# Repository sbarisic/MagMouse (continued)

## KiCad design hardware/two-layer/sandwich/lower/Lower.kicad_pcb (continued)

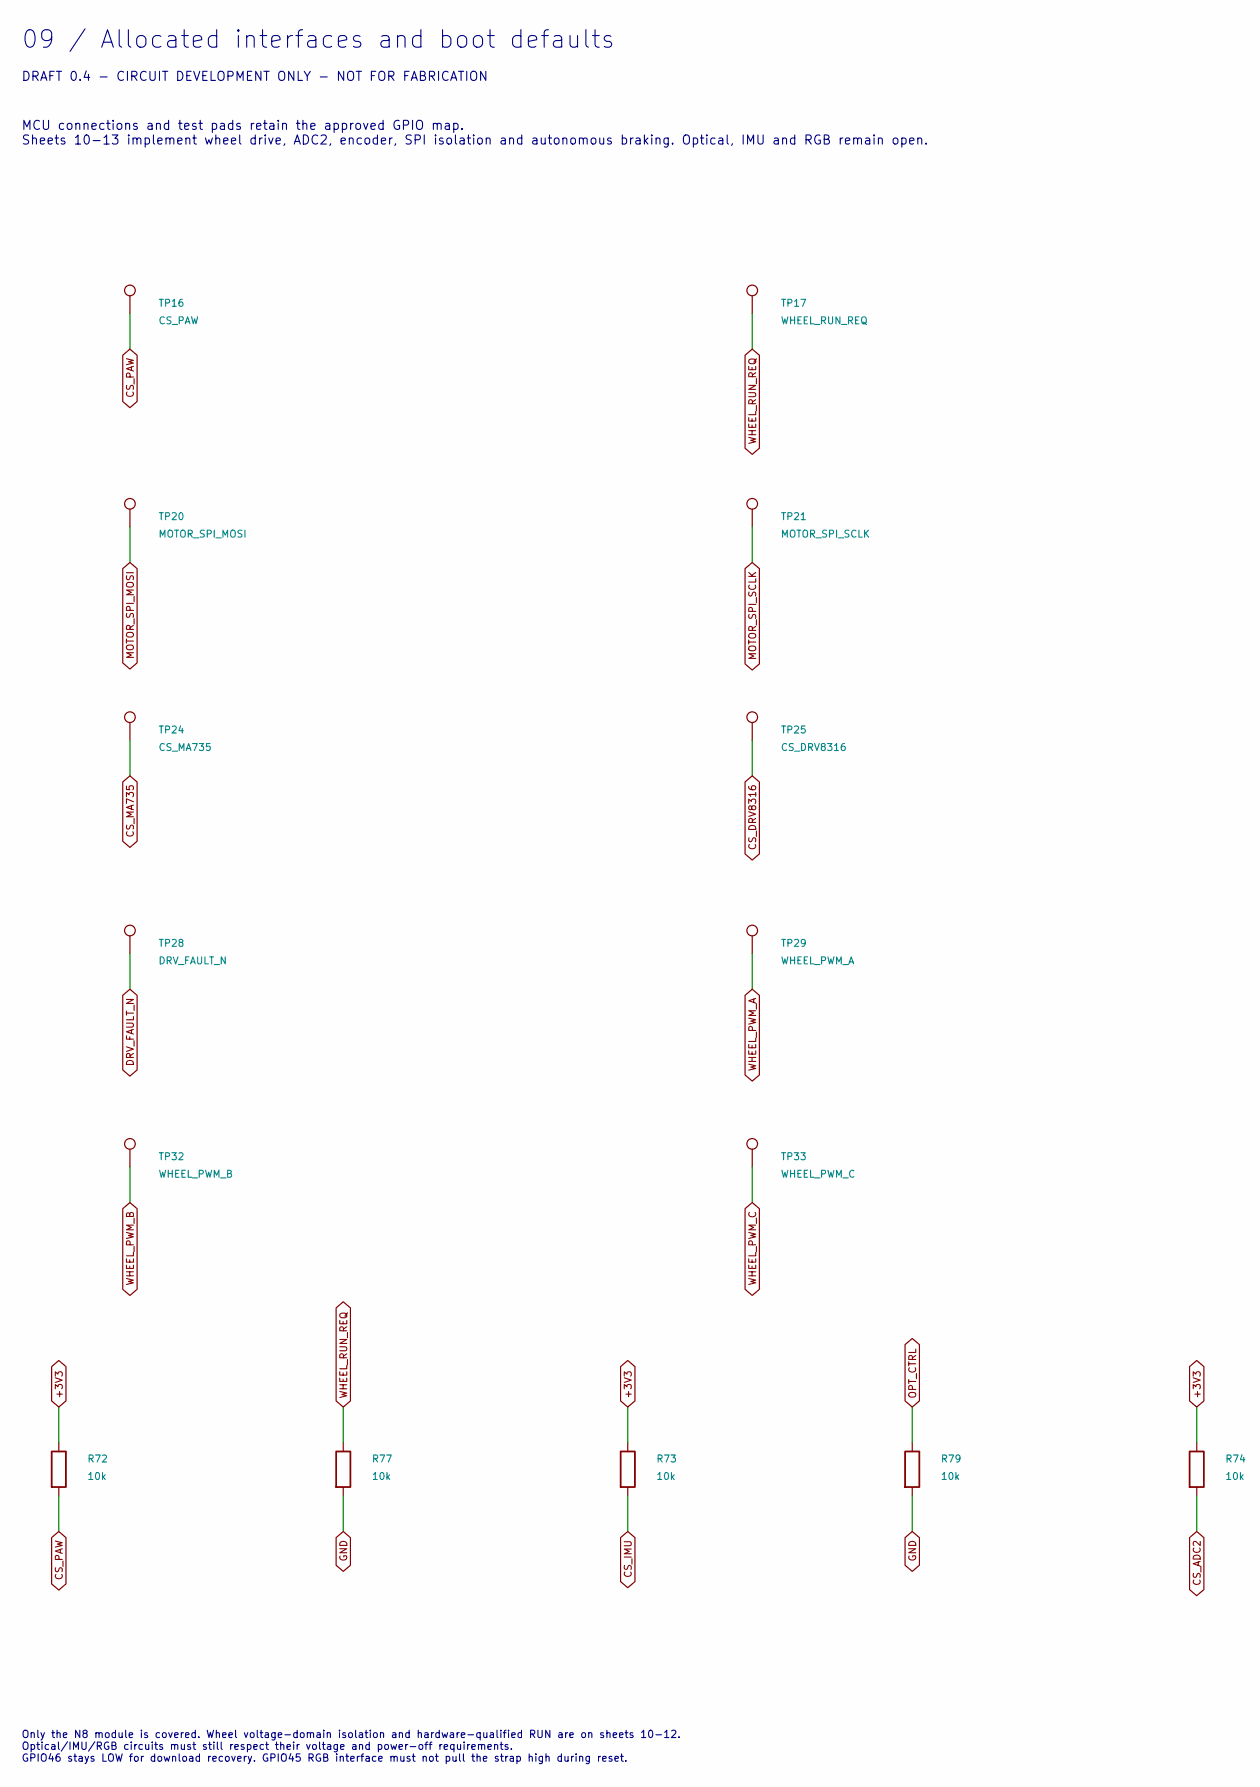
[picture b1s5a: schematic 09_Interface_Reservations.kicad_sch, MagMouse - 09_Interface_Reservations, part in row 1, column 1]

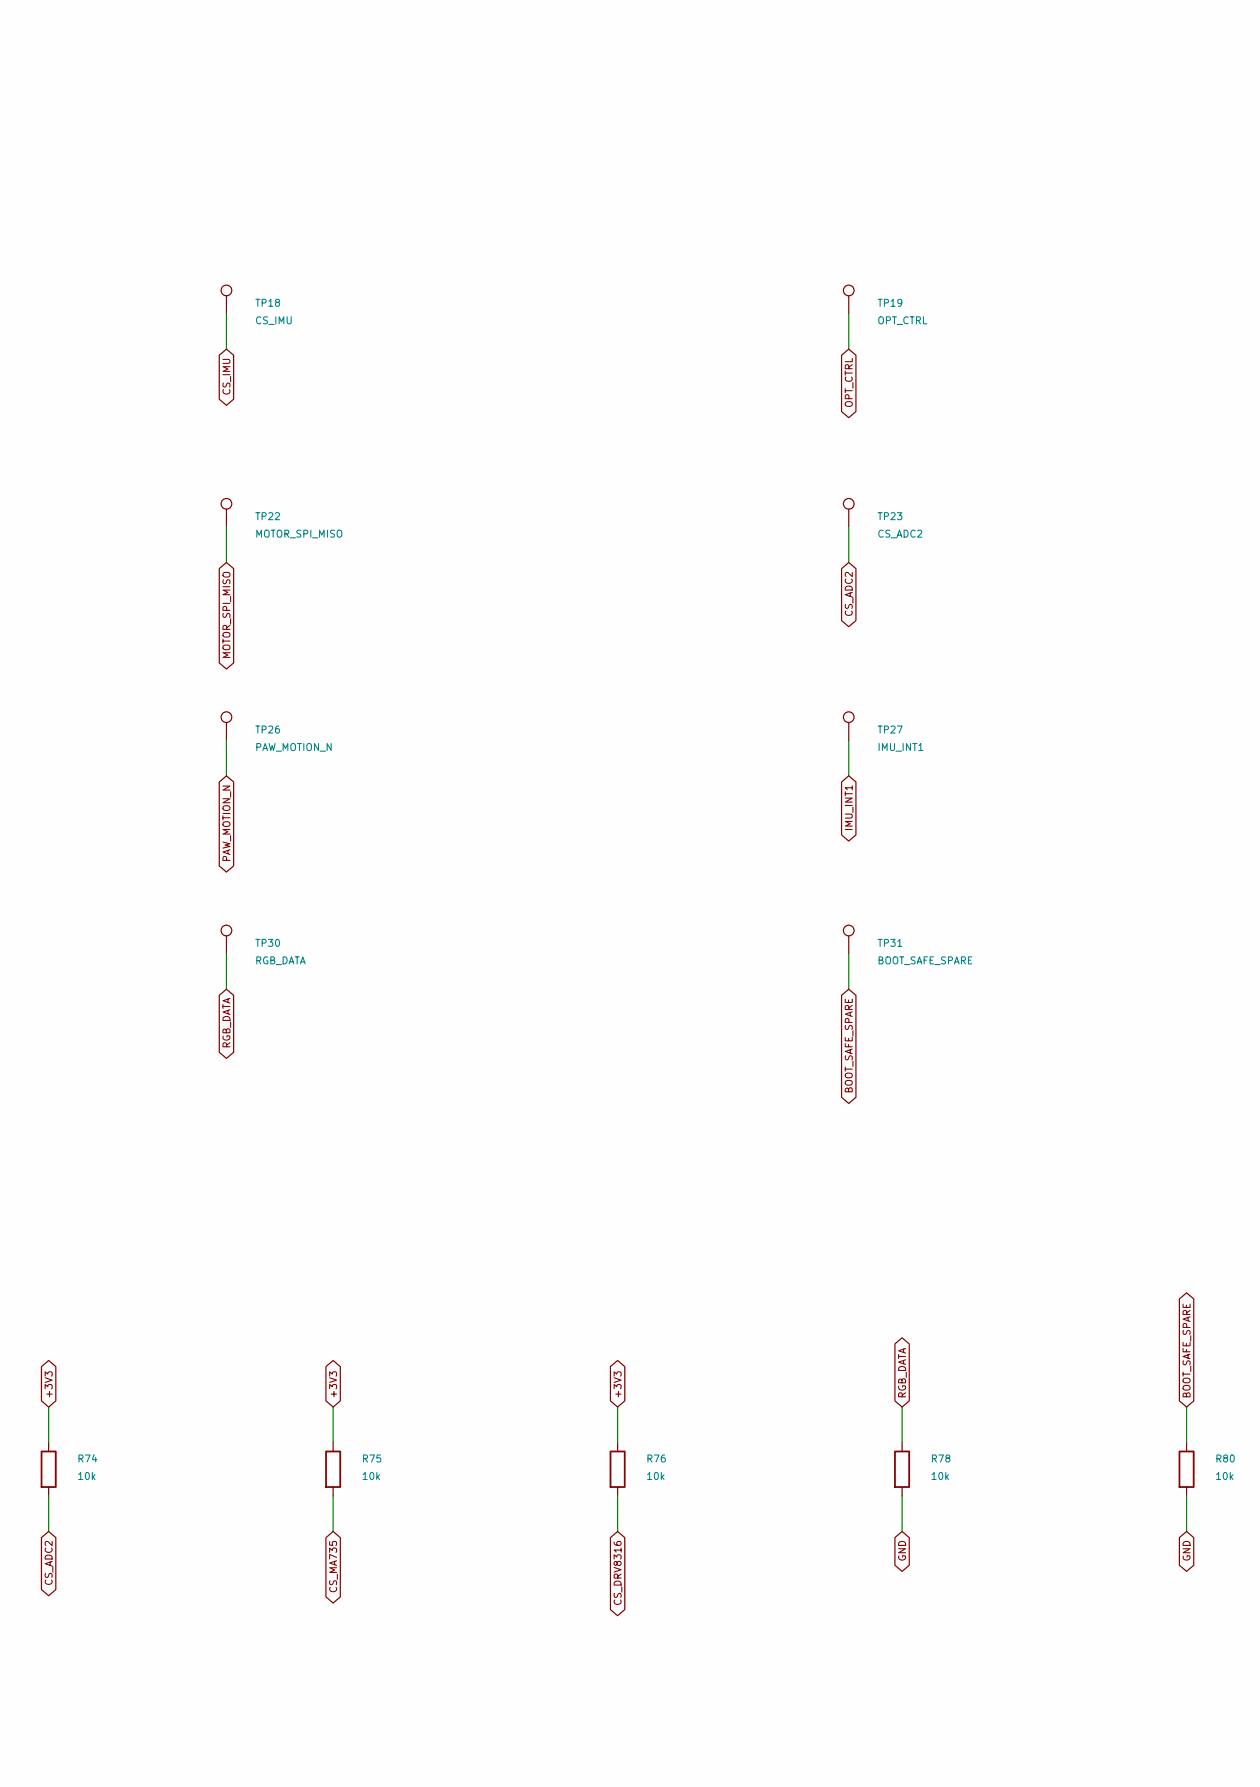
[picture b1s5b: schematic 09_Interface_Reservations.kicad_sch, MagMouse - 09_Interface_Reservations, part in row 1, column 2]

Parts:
R72, R73, R74, R75, R76, R77, R78, R79, R80: 10k; R_1206_3216Metric; Rating 0.25 W, 1%; MPN RC1206FR-0710KL
TP16: CS_PAW; TestPoint_Pad_D1.0mm
TP17: WHEEL_RUN_REQ; TestPoint_Pad_D1.0mm
TP18: CS_IMU; TestPoint_Pad_D1.0mm
TP19: OPT_CTRL; TestPoint_Pad_D1.0mm
TP20: MOTOR_SPI_MOSI; TestPoint_Pad_D1.0mm
TP21: MOTOR_SPI_SCLK; TestPoint_Pad_D1.0mm
TP22: MOTOR_SPI_MISO; TestPoint_Pad_D1.0mm
TP23: CS_ADC2; TestPoint_Pad_D1.0mm
TP24: CS_MA735; TestPoint_Pad_D1.0mm
TP25: CS_DRV8316; TestPoint_Pad_D1.0mm
TP26: PAW_MOTION_N; TestPoint_Pad_D1.0mm
TP27: IMU_INT1; TestPoint_Pad_D1.0mm
TP28: DRV_FAULT_N; TestPoint_Pad_D1.0mm
TP29: WHEEL_PWM_A; TestPoint_Pad_D1.0mm
TP30: RGB_DATA; TestPoint_Pad_D1.0mm
TP31: BOOT_SAFE_SPARE; TestPoint_Pad_D1.0mm
TP32: WHEEL_PWM_B; TestPoint_Pad_D1.0mm
TP33: WHEEL_PWM_C; TestPoint_Pad_D1.0mm

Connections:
+3V3: R72.1, R73.1, R74.1, R75.1, R76.1; also elsewhere on the board
BOOT_SAFE_SPARE: R80.1, TP31.1; also elsewhere on the board
CS_ADC2: R74.2, TP23.1; also elsewhere on the board
CS_DRV8316: R76.2, TP25.1; also elsewhere on the board
CS_IMU: R73.2, TP18.1; also elsewhere on the board
CS_MA735: R75.2, TP24.1; also elsewhere on the board
CS_PAW: R72.2, TP16.1; also elsewhere on the board
DRV_FAULT_N: TP28.1; also elsewhere on the board
GND: R77.2, R78.2, R79.2, R80.2; also elsewhere on the board
IMU_INT1: TP27.1; also elsewhere on the board
MOTOR_SPI_MISO: TP22.1; also elsewhere on the board
MOTOR_SPI_MOSI: TP20.1; also elsewhere on the board
MOTOR_SPI_SCLK: TP21.1; also elsewhere on the board
OPT_CTRL: R79.1, TP19.1; also elsewhere on the board
PAW_MOTION_N: TP26.1; also elsewhere on the board
RGB_DATA: R78.1, TP30.1; also elsewhere on the board
WHEEL_PWM_A: TP29.1; also elsewhere on the board
WHEEL_PWM_B: TP32.1; also elsewhere on the board
WHEEL_PWM_C: TP33.1; also elsewhere on the board
WHEEL_RUN_REQ: R77.1, TP17.1; also elsewhere on the board

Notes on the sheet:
09 / Allocated interfaces and boot defaults
DRAFT 0.4 - CIRCUIT DEVELOPMENT ONLY - NOT FOR FABRICATION
MCU connections and test pads retain the approved GPIO map. Sheets 10-13 implement wheel drive, ADC2, encoder, SPI isolation and autonomous braking. Optical, IMU and RGB remain open.
Only the N8 module is covered. Wheel voltage-domain isolation and hardware-qualified RUN are on sheets 10-12. Optical/IMU/RGB circuits must still respect their voltage and power-off requirements. GPIO46 stays LOW for download recovery. GPIO45 RGB interface must not pull the strap high during reset.

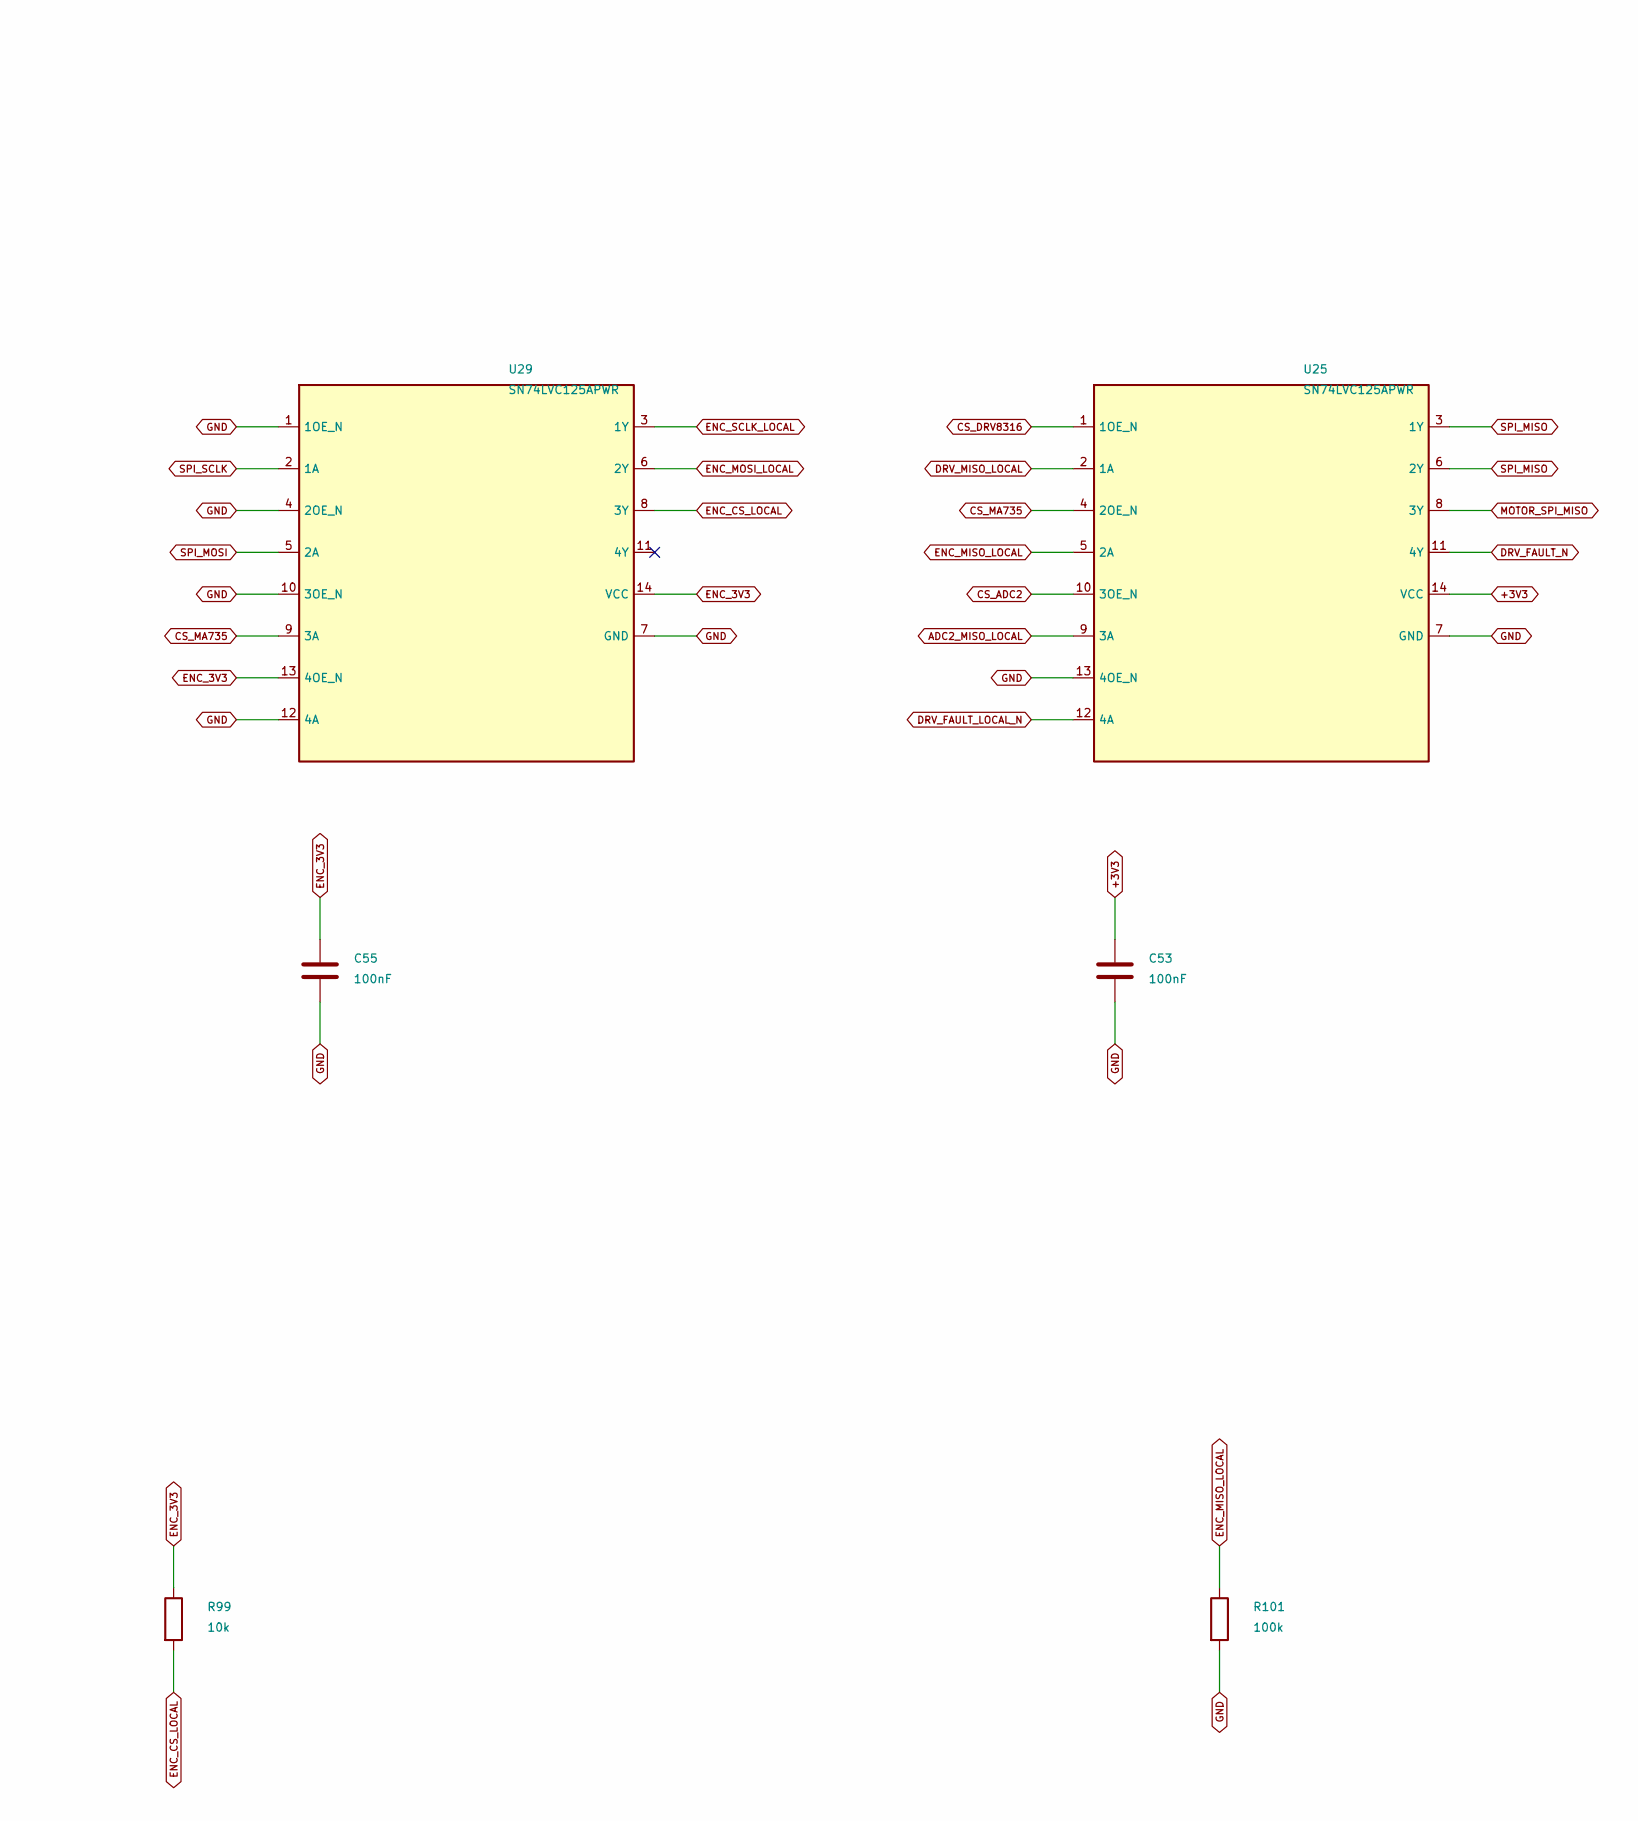
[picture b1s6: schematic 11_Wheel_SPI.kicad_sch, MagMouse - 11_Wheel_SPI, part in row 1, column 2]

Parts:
C53, C55: 100nF; C_1206_3216Metric; Rating 50 V, X7R, 10%; MPN CC1206KRX7R9BB104
R99: 10k; R_1206_3216Metric; Rating 0.25 W, 1%; MPN RC1206FR-0710KL
R101: 100k; R_1206_3216Metric; Rating 0.25 W, 1%; MPN RC1206FR-07100KL
U25, U29: SN74LVC125APWR; TSSOP-14_4.4x5mm_P0.65mm; MPN SN74LVC125APWR; LCSC C7813

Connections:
+3V3: C53.1, U25.14 (VCC); also elsewhere on the board
ADC2_MISO_LOCAL: U25.9 (3A); also elsewhere on the board
CS_ADC2: U25.10 (3OE_N); also elsewhere on the board
CS_DRV8316: U25.1 (1OE_N); also elsewhere on the board
CS_MA735: U25.4 (2OE_N), U29.9 (3A); also elsewhere on the board
DRV_FAULT_LOCAL_N: U25.12 (4A); also elsewhere on the board
DRV_FAULT_N: U25.11 (4Y); also elsewhere on the board
DRV_MISO_LOCAL: U25.2 (1A); also elsewhere on the board
ENC_3V3: C55.1, R99.1, U29.13 (4OE_N), U29.14 (VCC); also elsewhere on the board
ENC_CS_LOCAL: R99.2, U29.8 (3Y); also elsewhere on the board
ENC_MISO_LOCAL: R101.1, U25.5 (2A); also elsewhere on the board
ENC_MOSI_LOCAL: U29.6 (2Y); also elsewhere on the board
ENC_SCLK_LOCAL: U29.3 (1Y); also elsewhere on the board
GND: C53.2, C55.2, R101.2, U25.7 (GND), U25.13 (4OE_N), U29.1 (1OE_N), U29.4 (2OE_N), U29.7 (GND), U29.10 (3OE_N), U29.12 (4A); also elsewhere on the board
MOTOR_SPI_MISO: U25.8 (3Y); also elsewhere on the board
SPI_MISO: U25.3 (1Y), U25.6 (2Y); also elsewhere on the board
SPI_MOSI: U29.5 (2A); also elsewhere on the board
SPI_SCLK: U29.2 (1A); also elsewhere on the board

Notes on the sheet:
11_Wheel_SPI - Main owned components only See 18_Wheel_Harness for connector/bias additions; see INTERFACE_REVIEW.md for limits.

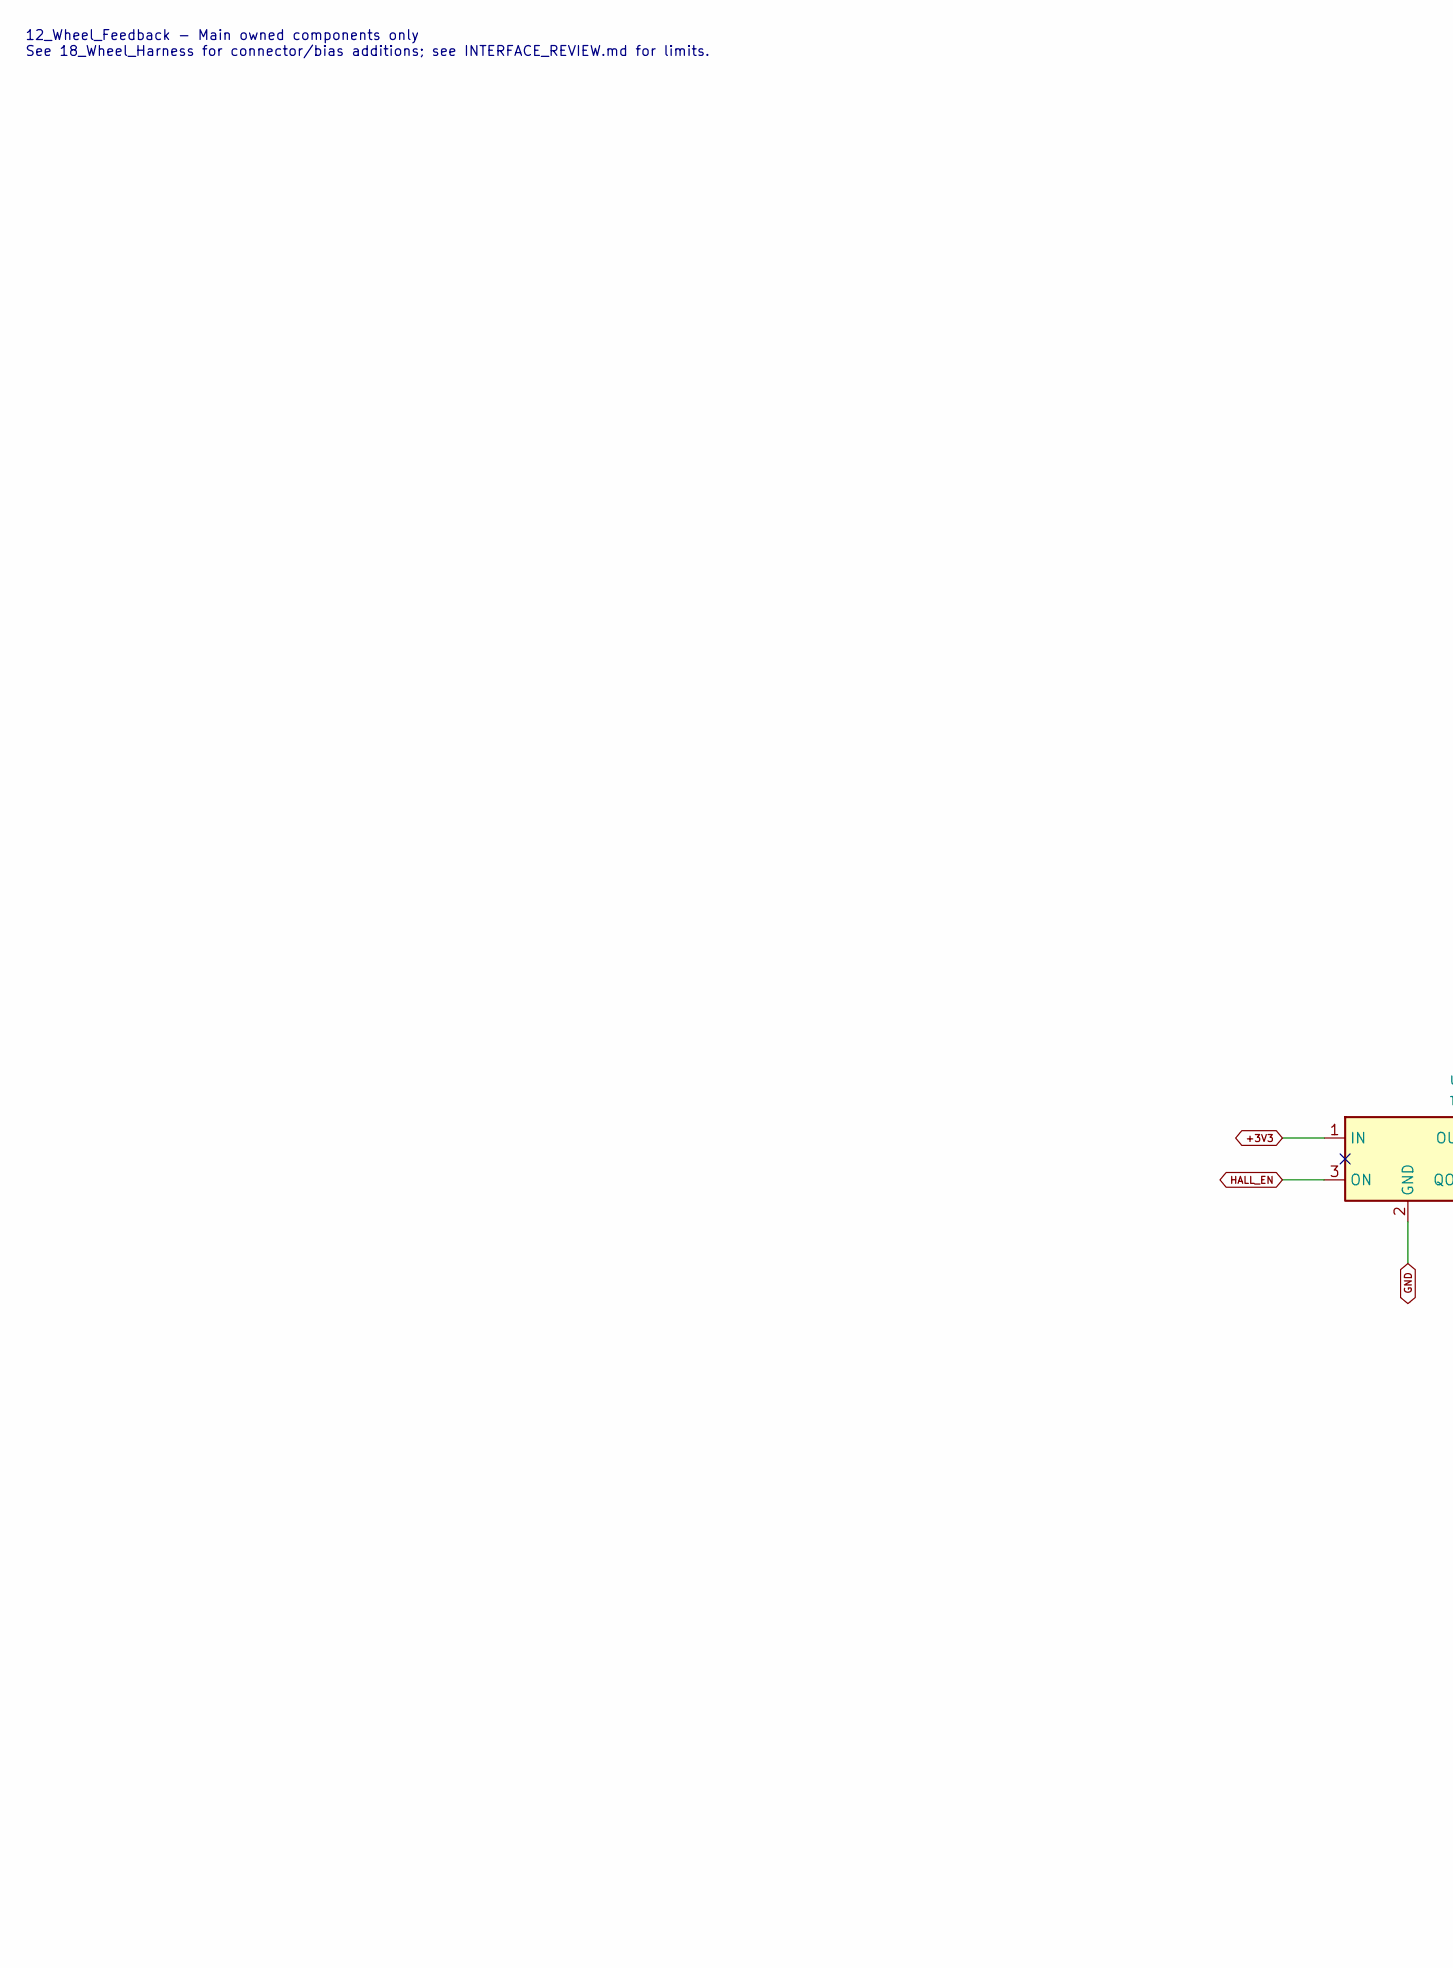
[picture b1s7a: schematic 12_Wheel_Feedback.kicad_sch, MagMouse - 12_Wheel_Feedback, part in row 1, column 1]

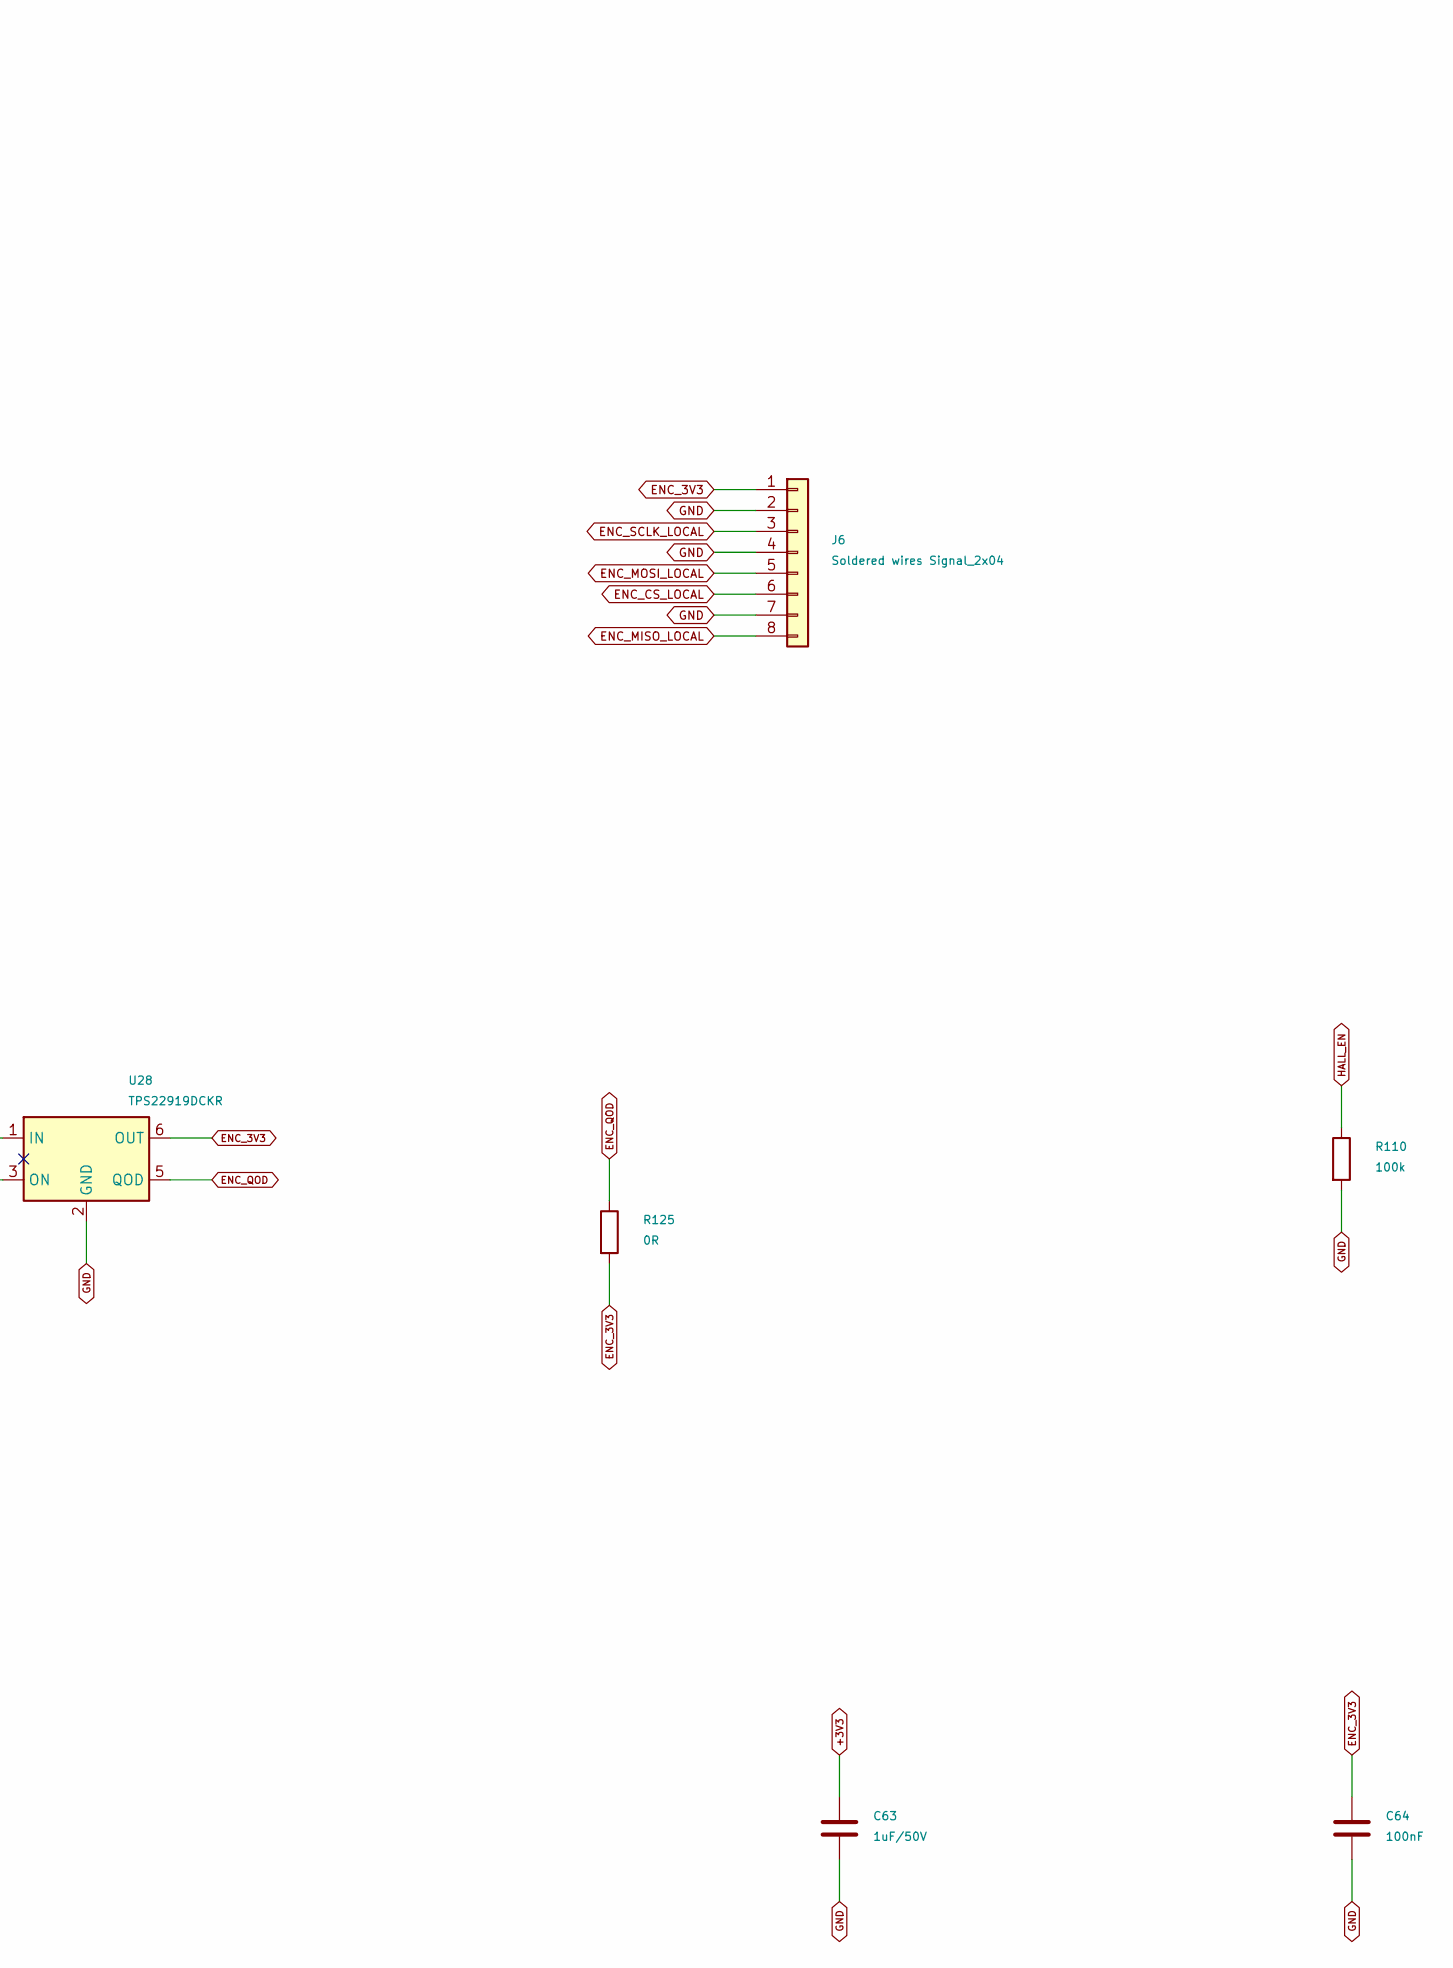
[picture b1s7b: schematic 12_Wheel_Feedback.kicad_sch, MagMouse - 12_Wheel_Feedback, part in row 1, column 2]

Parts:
C63: 1uF/50V; C_1206_3216Metric; Rating 50 V, X7R, 10%; MPN CL31B105KBHNNNE
C64: 100nF; C_1206_3216Metric; Rating 50 V, X7R, 10%; MPN CC1206KRX7R9BB104
J6: Soldered wires Signal_2x04; Wire_Signal_2x04_P2.54mm
R110: 100k; R_1206_3216Metric; Rating 0.25 W, 1%; MPN RC1206FR-07100KL
R125: 0R; R_1206_3216Metric; Rating Jumper, 2 A; MPN RC1206JR-070RL
U28: TPS22919DCKR; SOT-363_SC-70-6; MPN TPS22919DCKR; LCSC C2149796

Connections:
+3V3: C63.1, U28.1 (IN); also elsewhere on the board
ENC_3V3: C64.1, J6.1, R125.2, U28.6 (OUT); also elsewhere on the board
ENC_CS_LOCAL: J6.6; also elsewhere on the board
ENC_MISO_LOCAL: J6.8; also elsewhere on the board
ENC_MOSI_LOCAL: J6.5; also elsewhere on the board
ENC_QOD: R125.1, U28.5 (QOD)
ENC_SCLK_LOCAL: J6.3; also elsewhere on the board
GND: C63.2, C64.2, J6.2, J6.4, J6.7, R110.2, U28.2 (GND); also elsewhere on the board
HALL_EN: R110.1, U28.3 (ON); also elsewhere on the board

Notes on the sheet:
12_Wheel_Feedback - Main owned components only See 18_Wheel_Harness for connector/bias additions; see INTERFACE_REVIEW.md for limits.

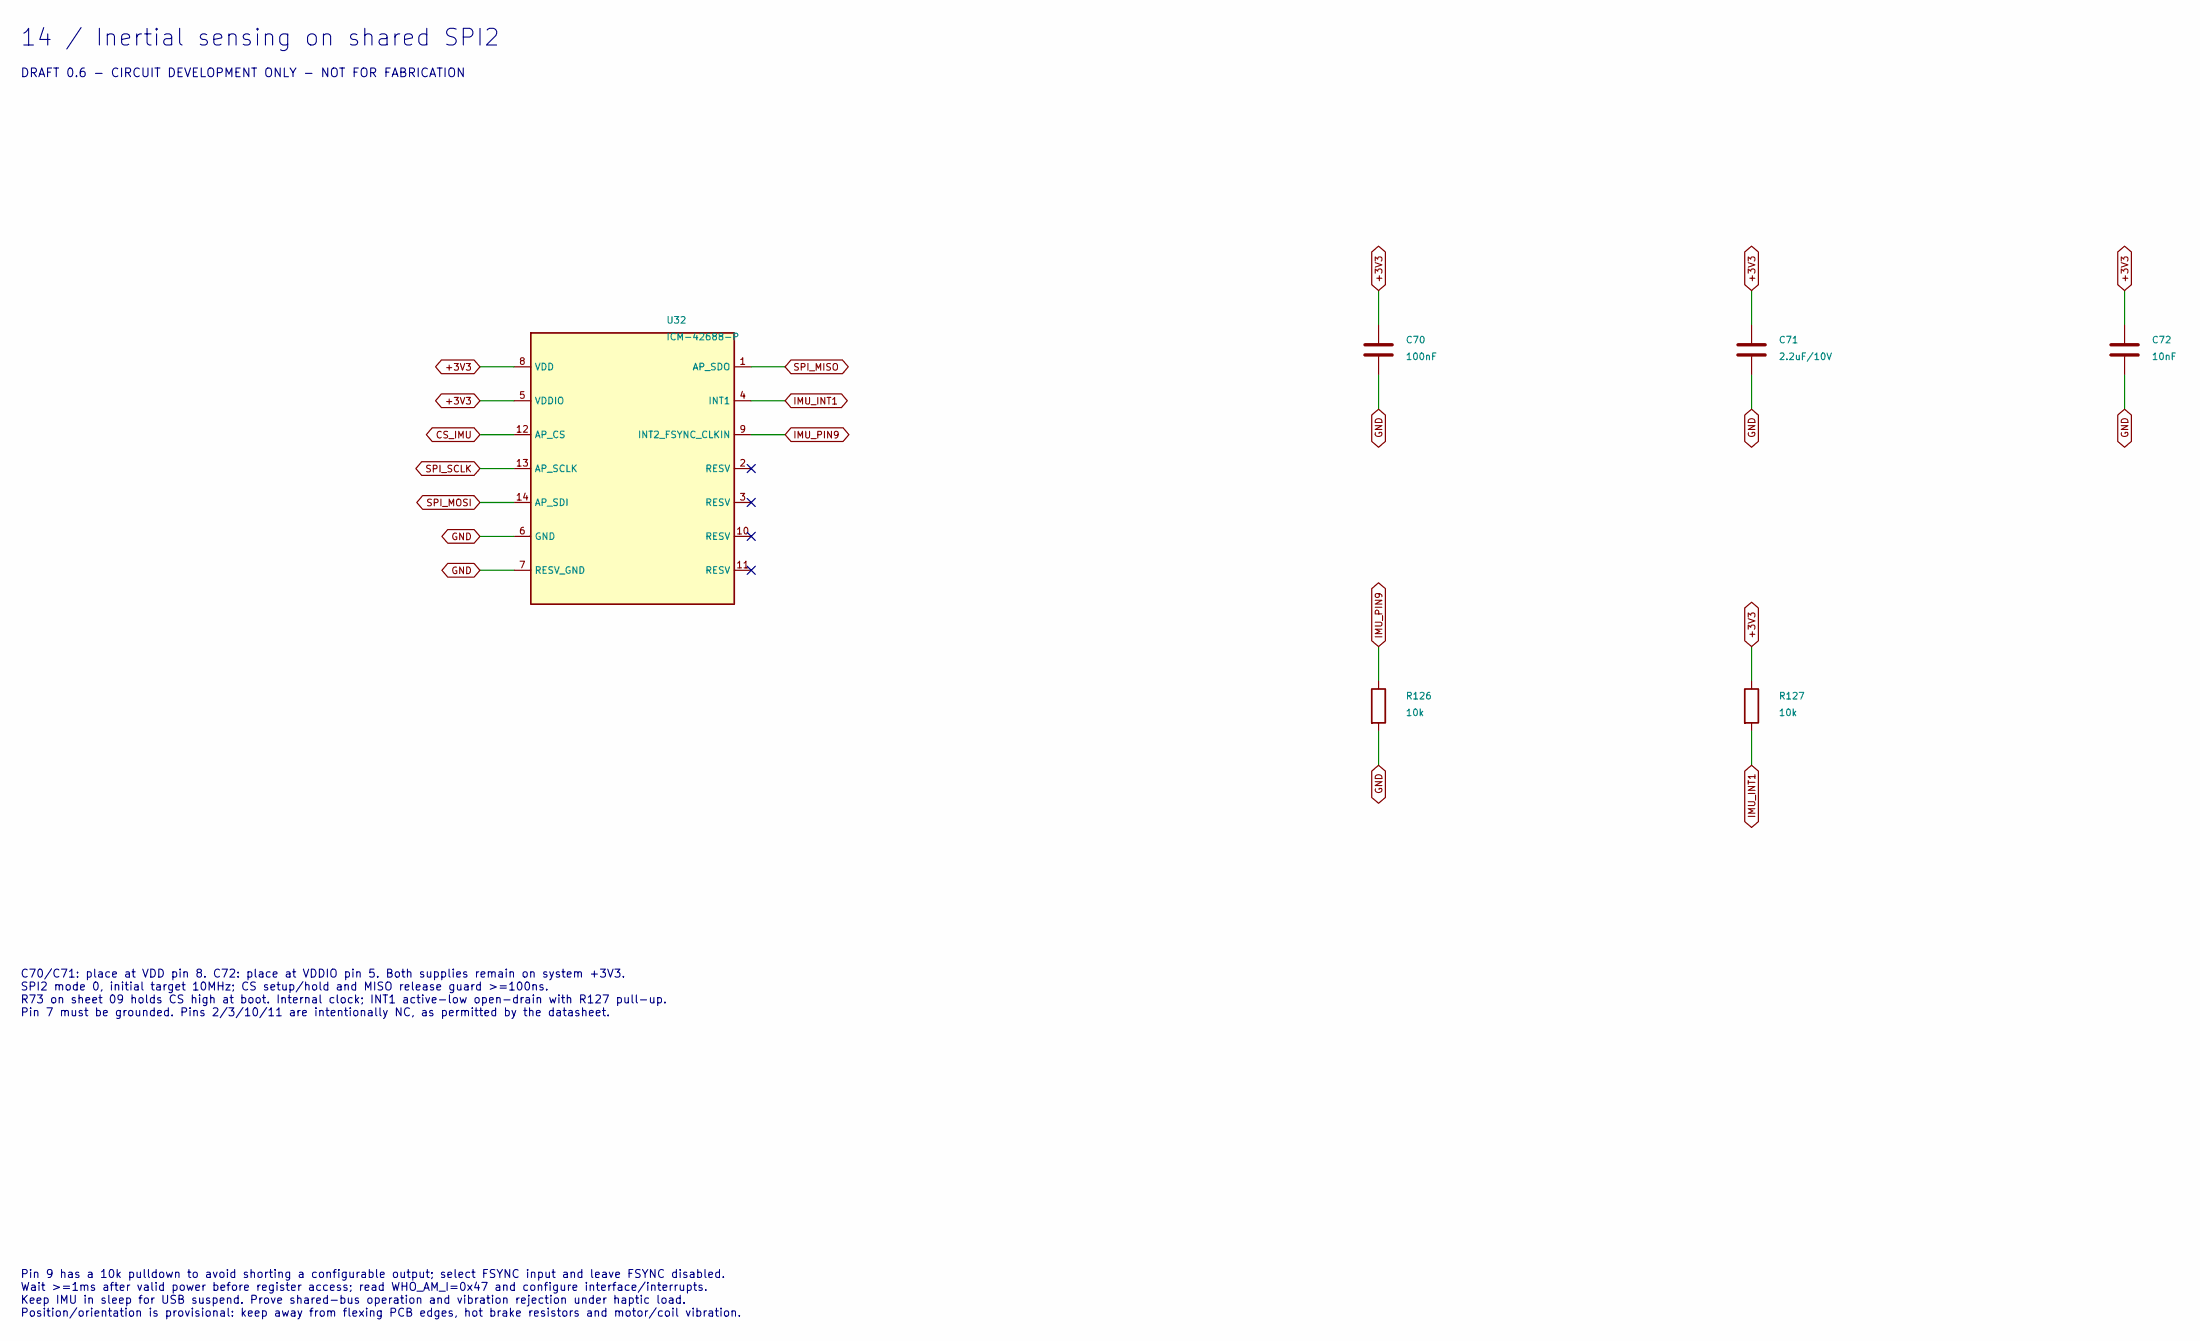
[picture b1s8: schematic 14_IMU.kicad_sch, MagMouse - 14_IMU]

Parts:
C70: 100nF; C_1206_3216Metric; Rating 50 V, X7R, 10%; MPN CC1206KRX7R9BB104
C71: 2.2uF/10V; C_1206_3216Metric; Rating 25 V, X7R, 10%; MPN CL31B225KAHNNNE
C72: 10nF; C_1206_3216Metric_OneSideSilk; Rating 50 V, X7R, 10%; MPN CC1206KRX7R9BB103
R126, R127: 10k; R_1206_3216Metric; Rating 0.25 W, 1%; MPN RC1206FR-0710KL
U32: ICM-42688-P; LGA-14_3x2.5mm_P0.5mm_LayoutBorder3x4y; MPN ICM-42688-P; LCSC C1850418

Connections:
+3V3: C70.1, C71.1, C72.1, R127.1, U32.5 (VDDIO), U32.8 (VDD); also elsewhere on the board
CS_IMU: U32.12 (AP_CS); also elsewhere on the board
GND: C70.2, C71.2, C72.2, R126.2, U32.6 (GND), U32.7 (RESV_GND); also elsewhere on the board
IMU_INT1: R127.2, U32.4 (INT1); also elsewhere on the board
IMU_PIN9: R126.1, U32.9 (INT2_FSYNC_CLKIN)
SPI_MISO: U32.1 (AP_SDO); also elsewhere on the board
SPI_MOSI: U32.14 (AP_SDI); also elsewhere on the board
SPI_SCLK: U32.13 (AP_SCLK); also elsewhere on the board

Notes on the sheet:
14 / Inertial sensing on shared SPI2
DRAFT 0.6 - CIRCUIT DEVELOPMENT ONLY - NOT FOR FABRICATION
C70/C71: place at VDD pin 8. C72: place at VDDIO pin 5. Both supplies remain on system +3V3. SPI2 mode 0, initial target 10MHz; CS setup/hold and MISO release guard >=100ns. R73 on sheet 09 holds CS high at boot. Internal clock; INT1 active-low open-drain with R127 pull-up. Pin 7 must be grounded. 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
Pin 9 has a 10k pulldown to avoid shorting a configurable output; select FSYNC input and leave FSYNC disabled. Wait >=1ms after valid power before register access; read WHO_AM_I=0x47 and configure interface/interrupts. Keep IMU in sleep for USB suspend. Prove shared-bus operation and vibration reje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

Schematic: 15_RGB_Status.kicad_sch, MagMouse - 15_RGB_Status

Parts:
C73, C74: 10uF/25V; C_1206_3216Metric; Rating 25 V, X5R, 10%; MPN CL31A106KAHNNNE
C75, C76: 100nF; C_1206_3216Metric; Rating 50 V, X7R, 10%; MPN CC1206KRX7R9BB104
D5: SK6805-EC15; OPSCO_SK6805_EC15; MPN SK6805-EC15; LCSC C2890035
R128: 330R; R_1206_3216Metric; Rating 0.25 W, 1%; MPN RC1206FR-07330RL
R129: 100k; R_1206_3216Metric; Rating 0.25 W, 1%; MPN RC1206FR-07100KL
R130: 10k; R_1206_3216Metric; Rating 0.25 W, 1%; MPN RC1206FR-0710KL
TP38: RGB_5V; TestPoint_Pad_D1.0mm
TP39: RGB_DIN; TestPoint_Pad_D1.0mm
U33: TPS7A2450DBVR; SOT-23-5; MPN TPS7A2450DBVR; LCSC C2864436
U34: SN74LV1T34DBVR; SOT-23-5; MPN SN74LV1T34DBVR; LCSC C100024

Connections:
GND: C73.2, C74.2, C75.2, C76.2, D5.4 (GND), R129.2, R130.2, U33.2 (GND), U34.3 (GND); also elsewhere on the board
HALL_EN: U33.3 (EN); also elsewhere on the board
PWR_5V: C73.1, U33.1 (IN); also elsewhere on the board
RGB_5V: C74.1, C75.1, C76.1, D5.2 (VDD), R130.1, TP38.1, U33.5 (OUT), U34.5 (VCC)
RGB_BUFFER_OUT: R128.1, U34.4 (Y)
RGB_DATA: U34.2 (A); also elsewhere on the board
RGB_DIN: D5.1 (DIN), R128.2, R129.1, TP39.1

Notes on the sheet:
15 / Single-data-pin status LED with switched protected supply
DRAFT 0.6 - CIRCUIT DEVELOPMENT ONLY - NOT FOR FABRICATION
U33 caps the LED rail near 5V; in dropout RGB_5V follows PWR_5V minus dropout. This is not a boost supply. HALL_EN low disables RGB with Hall/encoder sleep; R130 discharges local storage. ACT_5V is never used. U34 shifts 3.3V data to the LED rail. R78 on sheet 09 preserves GPIO45 boot-low; no LED-r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
Firmware: hold data low during rail transitions; send black before suspend, then lower HALL_EN. Target 800kbps GRB/MSB-first; A1 timing 0=0.30/0.95us, 1=0.90/0.35us, reset low >=300us. Qualify startup/dropout, discharge, bus current and RGB_DIN timing on hardware. LED supply must stay 3.7..5.5V.

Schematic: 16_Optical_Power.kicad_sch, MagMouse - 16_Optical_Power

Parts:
C77, C78: 10uF/25V; C_1206_3216Metric; Rating 25 V, X5R, 10%; MPN CL31A106KAHNNNE
C79: 1nF/50V; C_1206_3216Metric; Rating 50 V, X7R, 10%; MPN CC1206KRX7R9BB102
C81, C82: 2.2uF/10V; C_1206_3216Metric; Rating 25 V, X7R, 10%; MPN CL31B225KAHNNNE
C83, C85: 100nF; C_1206_3216Metric; Rating 50 V, X7R, 10%; MPN CC1206KRX7R9BB104
C84: 4.7uF/10V; C_1206_3216Metric; Rating 25 V, X5R, 10%; MPN CL31A475KAHNNNE
R132: 39R; R_1206_3216Metric; Rating 0.25 W, 1%; MPN RC1206FR-0739RL
TP40: OPT_3V3; TestPoint_Pad_D1.0mm
TP41: OPT_1V9; TestPoint_Pad_D1.0mm
TP42: OPT_VDDPIX; TestPoint_Pad_D1.0mm
U36: TLV75519PDBVR; SOT-23-5; MPN TLV75519PDBVR; LCSC C2865381
U38: TPS22918DBVR; SOT-23-6; MPN TPS22918DBVR; LCSC C131941

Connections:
+3V3: C77.1, C78.1, U38.1 (VIN); also elsewhere on the board
GND: C77.2, C78.2, C79.2, C81.2, C82.2, C83.2, C84.2, C85.2, U36.2 (GND), U38.2 (GND); also elsewhere on the board
HALL_EN: U38.3 (ON); also elsewhere on the board
OPT_1V9: C82.1, C83.1, R132.1, TP41.1, U36.5 (OUT); also elsewhere on the board
OPT_3V3: C81.1, TP40.1, U36.1 (IN), U36.3 (EN), U38.6 (VOUT); also elsewhere on the board
OPT_LED_P: R132.2; also elsewhere on the board
OPT_RAMP_CT: C79.1, U38.4 (CT)
OPT_VDDPIX: C84.1, C85.1, TP42.1; also elsewhere on the board

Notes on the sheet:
16_Optical_Power - Main owned components only See 18_Wheel_Harness for connector/bias additions; see INTERFACE_REVIEW.md for limits.

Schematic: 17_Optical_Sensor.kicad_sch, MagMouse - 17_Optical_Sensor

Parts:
C80, C86, C87: 100nF; C_1206_3216Metric; Rating 50 V, X7R, 10%; MPN CC1206KRX7R9BB104
R131, R135: 10k; R_1206_3216Metric; Rating 0.25 W, 1%; MPN RC1206FR-0710KL
R133, R134, R136: 100k; R_1206_3216Metric; Rating 0.25 W, 1%; MPN RC1206FR-07100KL
TP43: OPT_RESET_N; TestPoint_Pad_D1.0mm
U35: PMW3360DM-T2QU; PixArt_PMW3360DM_T2QU; MPN PMW3360DM-T2QU; LCSC C20612443
U37: SN74LVC125APWR; TSSOP-14_4.4x5mm_P0.65mm; MPN SN74LVC125APWR; LCSC C7813
U39: SN74LVC1G125DBVR; SOT-23-5; MPN SN74LVC1G125DBVR; LCSC C23654

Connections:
CS_PAW: U37.1 (1OE_N), U37.4 (2OE_N), U37.10 (3OE_N), U39.2 (A); also elsewhere on the board
GND: C80.2, C86.2, C87.2, R134.2, U35.8 (GND), U37.7 (GND), U37.13 (4OE_N), U39.1 (OE_N), U39.3 (GND); also elsewhere on the board
OPT_1V9: U35.4 (VDD_1V9); also elsewhere on the board
OPT_3V3: C80.1, C86.1, C87.1, R131.1, R133.1, R135.1, R136.1, U35.5 (VDDIO), U37.14 (VCC), U39.5 (VCC); also elsewhere on the board
OPT_CS_N: R131.2, U35.13 (NCS), U39.4 (Y)
OPT_CTRL: U37.12 (4A); also elsewhere on the board
OPT_LED_P: U35.15 (LED_P); also elsewhere on the board
OPT_MISO: R135.2, U35.12 (MISO), U37.9 (3A)
OPT_MOSI: R134.1, U35.11 (MOSI), U37.3 (1Y)
OPT_RESET_N: TP43.1, U35.7 (NRESET), U37.11 (4Y)
OPT_SCLK: R133.2, U35.10 (SCLK), U37.6 (2Y)
OPT_VDDPIX: U35.3 (VDDPIX_OUT); also elsewhere on the board
PAW_MOTION_N: R136.2, U35.9 (MOTION); also elsewhere on the board
SPI_MISO: U37.8 (3Y); also elsewhere on the board
SPI_MOSI: U37.2 (1A); also elsewhere on the board
SPI_SCLK: U37.5 (2A); also elsewhere on the board

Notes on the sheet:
17 / PMW3360 with selected-device SPI isolation and buffered reset
DRAFT 0.7 - CIRCUIT DEVELOPMENT ONLY - NOT FOR FABRICATION
SPI2 mode 3, <=2MHz. Set SCLK high before selecting; CS setup/read hold/release guard >=1us. U37 disconnects sensor clock, MOSI and MISO while CS_PAW is high; reset channel is always enabled. R72 holds CS high and R79 holds OPT_CTRL low at boot. Keep all CS high during reset and rail transitions. S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
OPT_CTRL low asserts reset despite the internal pull-up (600uA max). U39 isolates CS when unpowered. After valid rails: reset, wait >=50ms, clear motion registers, load authorized SROM and verify identity. Suspend: send Shutdown, deselect, assert reset, clear SENS_REQ. Resume requires full initiali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
